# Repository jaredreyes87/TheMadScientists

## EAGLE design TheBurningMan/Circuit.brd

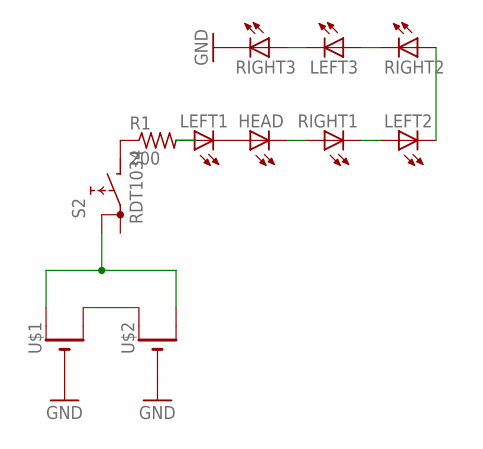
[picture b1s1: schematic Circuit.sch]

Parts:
HEAD: LED3MM
LEFT1, LEFT2, LEFT3: LED3MM
R1: 200; 0204V
RIGHT1, RIGHT2, RIGHT3: LED3MM
S2: RDT1034
U$1, U$2: CR1220THM; CR1220-THM

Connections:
GND: RIGHT3.K (C), U$1.-, U$2.-
unnamed: U$1.+2 (+1), U$2.+1 (+)
unnamed: S2.A, U$1.+1 (+), U$2.+2 (+1)
unnamed: LEFT1.A, R1.2
unnamed: HEAD.A, LEFT1.K (C)
unnamed: HEAD.K (C), RIGHT1.A
unnamed: LEFT2.A, RIGHT1.K (C)
unnamed: LEFT3.A, RIGHT2.K (C)
unnamed: LEFT2.K (C), RIGHT2.A
unnamed: LEFT3.K (C), RIGHT3.A
unnamed: R1.1, S2.B

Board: 2 copper layers, 11 parts (0 on the bottom side), 11 nets, no tracks yet.

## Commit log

2018-04-17 Create test
